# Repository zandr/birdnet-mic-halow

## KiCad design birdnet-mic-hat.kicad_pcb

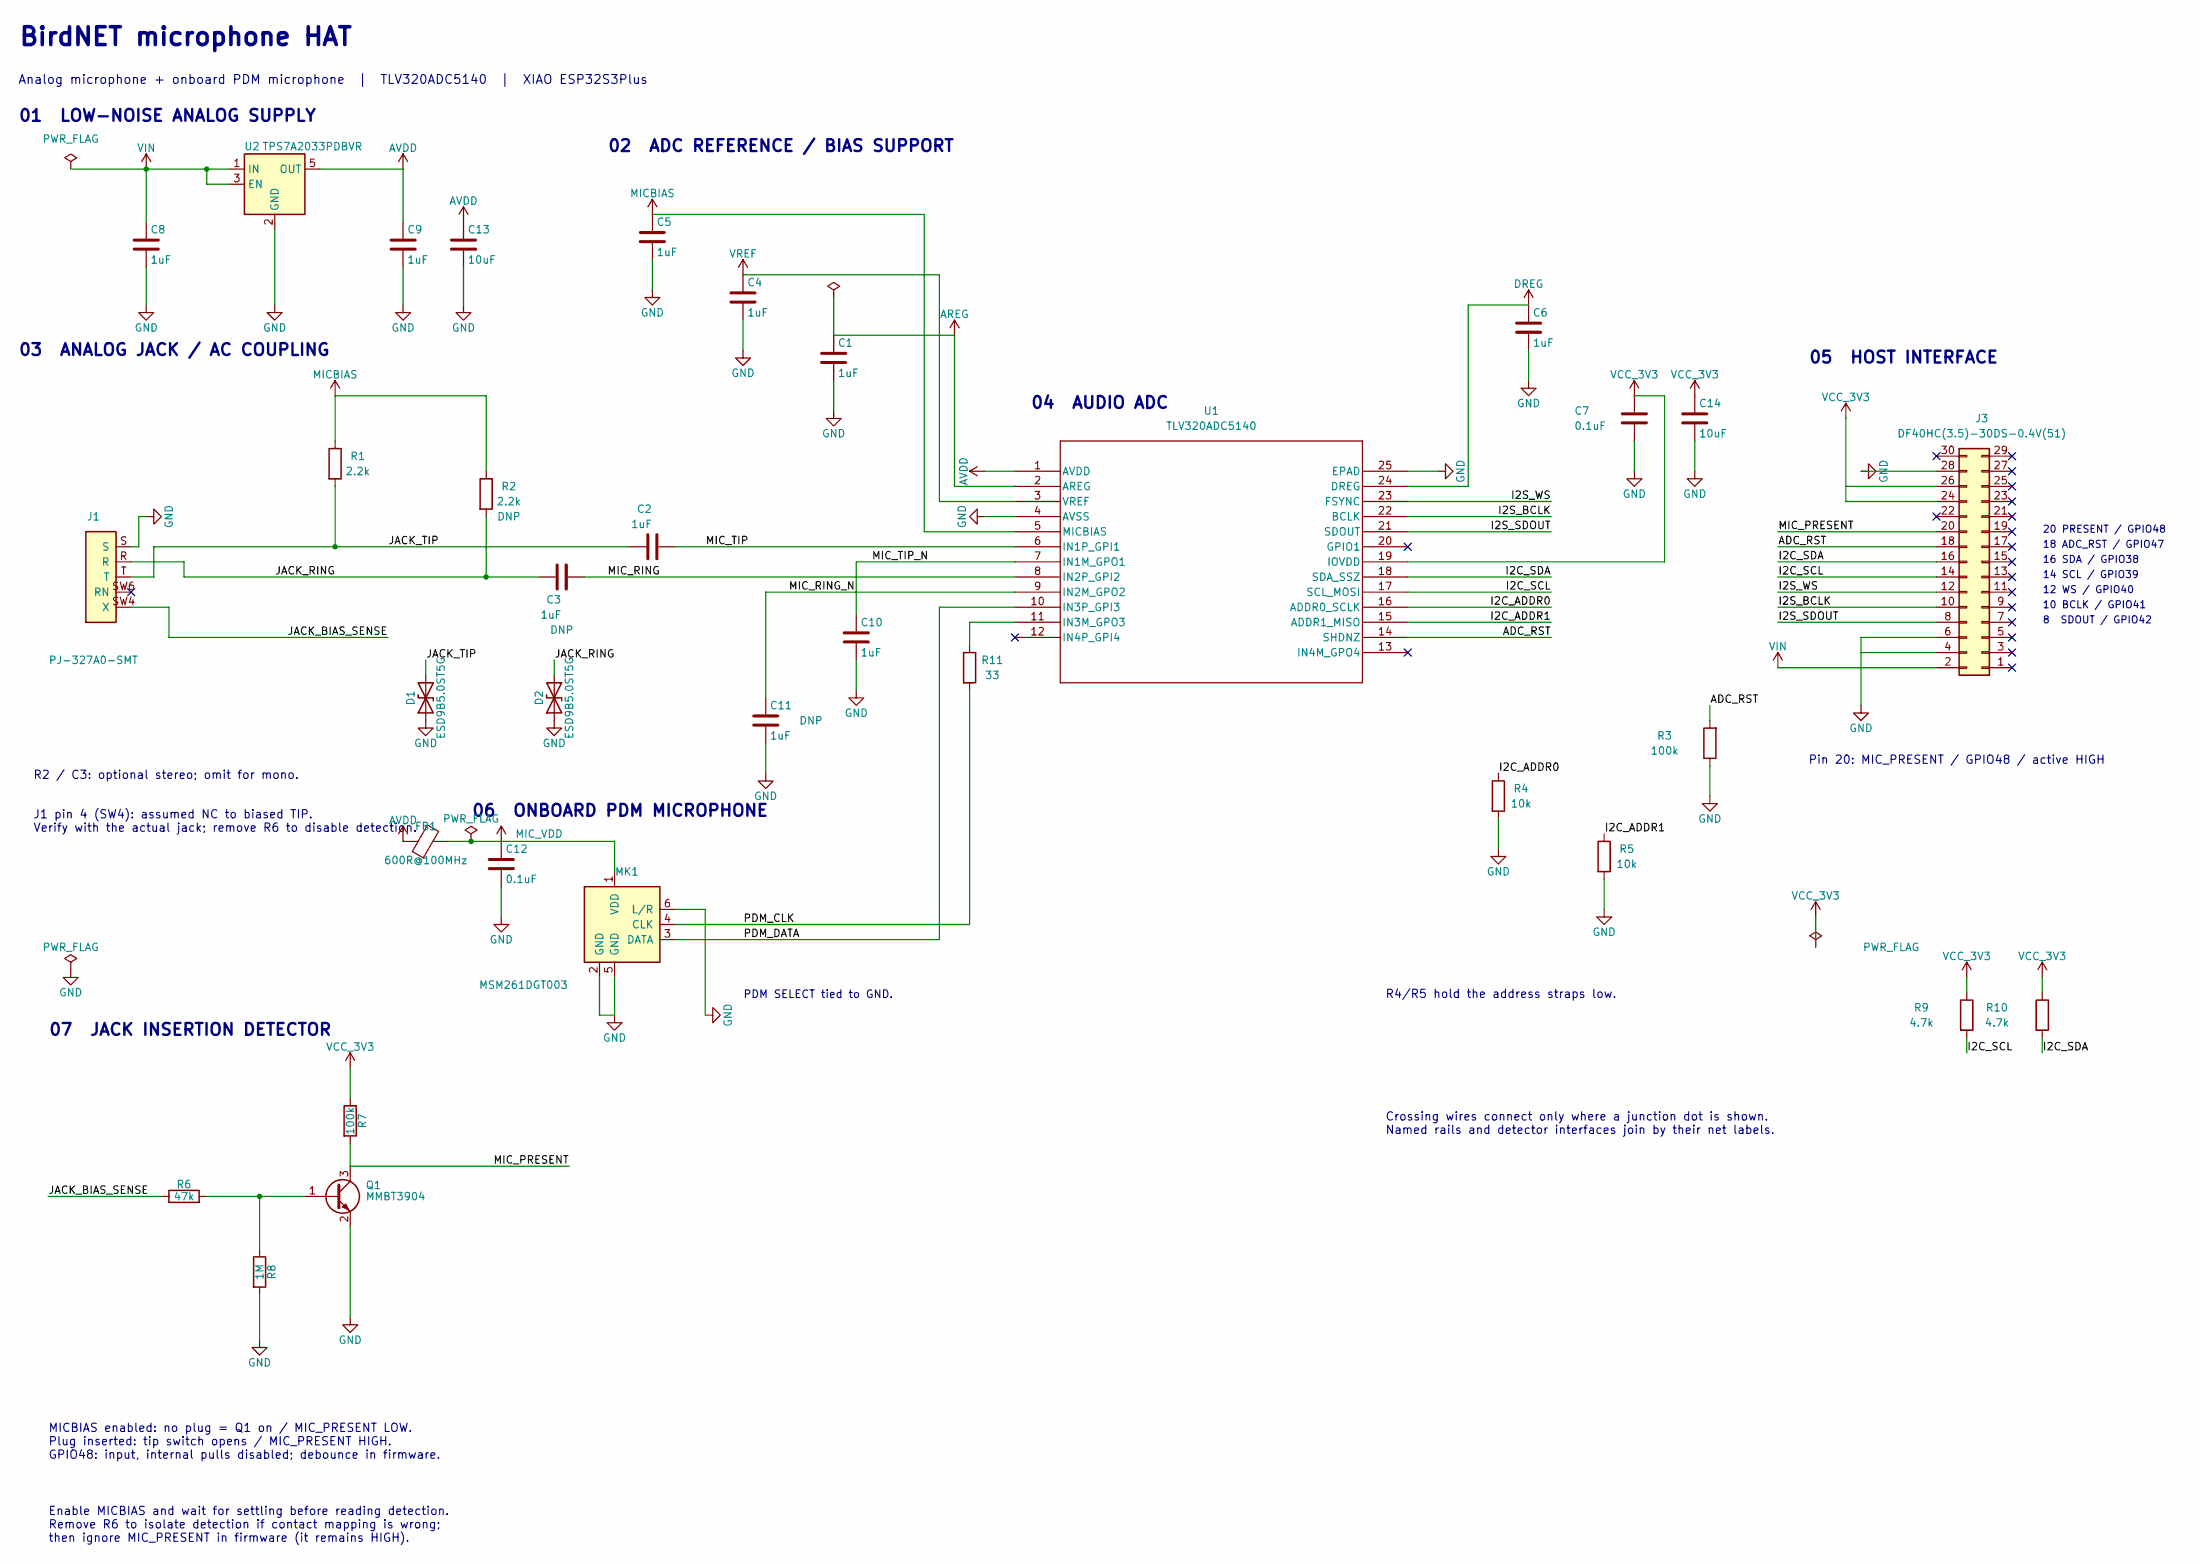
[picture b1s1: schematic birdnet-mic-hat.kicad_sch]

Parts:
C1, C4, C5, C6, C8, C9: 1uF; C_0402_1005Metric
C2, C3, C10, C11: 1uF; C_0603_1608Metric
C7, C12: 0.1uF; C_0402_1005Metric
C13, C14: 10uF; C_0603_1608Metric; MPN CL10A106KP8NNNC; LCSC C19702
D1, D2: ESD9B5.0ST5G; D_SOD-923; MPN ESD9B5.0ST5G; LCSC C111566
FB1: 600R@100MHz; L_0402_1005Metric; MPN BLM15PX601SN1D; LCSC C160977
J1: PJ-327A0-SMT; Jack_3.5mm_PJ-327A0-SMT; LCSC C381135
J3: DF40HC(3.5)-30DS-0.4V(51); DF40_30_LongWave_Hat
MK1: MSM261DGT003; MPN MSM261DGT003; LCSC C48227730
Q1: MMBT3904; SOT-23; MPN MMBT3904; LCSC C20526
R1, R2: 2.2k; R_0402_1005Metric
R3, R7: 100k; R_0402_1005Metric
R4, R5: 10k; R_0402_1005Metric
R6: 47k; R_0402_1005Metric
R8: 1M; R_0402_1005Metric
R9, R10: 4.7k; R_0402_1005Metric
R11: 33; R_0402_1005Metric
U1: TLV320ADC5140; RTW24_4P15X4P15_TEX
U2: TPS7A2033PDBVR; SOT-23-5

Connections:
/ADC_RST: J3.18, R3.2, U1.14 (SHDNZ)
/I2C_ADDR0: R4.1, U1.16 (ADDR0_SCLK)
/I2C_ADDR1: R5.1, U1.15 (ADDR1_MISO)
/I2C_SCL: J3.14, R9.2, U1.17 (SCL_MOSI)
/I2C_SDA: J3.16, R10.2, U1.18 (SDA_SSZ)
/I2S_BCLK: J3.10, U1.22 (BCLK)
/I2S_SDOUT: J3.8, U1.21 (SDOUT)
/I2S_WS: J3.12, U1.23 (FSYNC)
/JACK_BIAS_SENSE: J1.SW4 (X), R6.1
/JACK_RING: C3.1, D2.2 (A2), J1.R, R2.2
/JACK_TIP: C2.1, D1.2 (A2), J1.T, R1.2
/MIC_PRESENT: J3.20, Q1.3 (C), R7.2
/MIC_RING: C3.2, U1.8 (IN2P_GPI2)
/MIC_RING_N: C11.1, U1.9 (IN2M_GPO2)
/MIC_TIP: C2.2, U1.6 (IN1P_GPI1)
/MIC_TIP_N: C10.1, U1.7 (IN1M_GPO1)
/PDM_CLK: MK1.4 (CLK), R11.2
/PDM_DATA: MK1.3 (DATA), U1.10 (IN3P_GPI3)
AREG: C1.1, U1.2 (AREG)
AVDD: C9.1, C13.1, FB1.1, U1.1 (AVDD), U2.5 (OUT)
DREG: C6.1, U1.24 (DREG)
GND: C1.2, C4.2, C5.2, C6.2, C7.2, C8.2, C9.2, C10.2, C11.2, C12.2, C13.2, C14.2, D1.1 (A1), D2.1 (A1), J1.S, J3.4, J3.6, J3.28, MK1.2 (GND), MK1.5 (GND), MK1.6 (L/R), Q1.2 (E), R3.1, R4.2, R5.2, R8.2, U1.4 (AVSS), U1.25 (EPAD), U2.2 (GND)
MICBIAS: C5.1, R1.1, R2.1, U1.5 (MICBIAS)
MIC_VDD: C12.1, FB1.2, MK1.1 (VDD)
unnamed: Q1.1 (B), R6.2, R8.1
unnamed: R11.1, U1.11 (IN3M_GPO3)
VCC_3V3: C7.1, C14.1, J3.24, J3.26, R7.1, R9.1, R10.1, U1.19 (IOVDD)
VIN: C8.1, J3.2, U2.1 (IN), U2.3 (EN)
VREF: C4.1, U1.3 (VREF)

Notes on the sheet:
R4/R5 hold the address straps low.
02 ADC REFERENCE / BIAS SUPPORT
16 SDA / GPIO38
12 WS / GPIO40
8 SDOUT / GPIO42
Pin 20: MIC_PRESENT / GPIO48 / active HIGH
14 SCL / GPIO39
01 LOW-NOISE ANALOG SUPPLY
06 ONBOARD PDM MICROPHONE
R2 / C3: optional stereo; omit for mono.
18 ADC_RST / GPIO47
MICBIAS enabled: no plug = Q1 on / MIC_PRESENT LOW. Plug inserted: tip switch opens / MIC_PRESENT HIGH. GPIO48: input, internal pulls disabled; debounce in firmware.
J1 pin 4 (SW4): assumed NC to biased TIP. Verify with the actual jack; remove R6 to disable detection.
20 PRESENT / GPIO48
10 BCLK / GPIO41
04 AUDIO ADC
PDM SELECT tied to GND.
BirdNET microphone HAT
Enable MICBIAS and wait for settling before reading detection. Remove R6 to isolate detection if contact mapping is wrong; then ignore MIC_PRESENT in firmware (it remains HIGH).
03 ANALOG JACK / AC COUPLING
Crossing wires connect only where a junction dot is shown. Named rails and detector interfaces join by their net labels.
Analog microphone + onboard PDM microphone | TLV320ADC5140 | XIAO ESP32S3Plus
07 JACK INSERTION DETECTOR
05 HOST INTERFACE

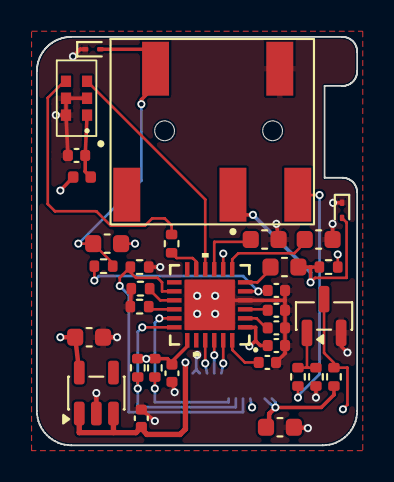
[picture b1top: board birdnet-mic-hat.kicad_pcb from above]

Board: 4 copper layers, 17.8 x 22.7 mm, 34 parts (1 on the bottom side), 29 nets.

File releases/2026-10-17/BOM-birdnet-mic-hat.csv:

Comment,Designator,Footprint,LCSC Part #,MPN,Manufacturer,Quantity
1uF,"C1,C4,C5,C6,C8,C9",Capacitor_SMD:C_0402_1005Metric,C167339,0402X105K160NT,FH,6
1uF,"C2,C10",Capacitor_SMD:C_0603_1608Metric,C106248,CC0603KRX7R7BB105,YAGEO,2
0.1uF,"C7,C12",Capacitor_SMD:C_0402_1005Metric,C60474,CC0402KRX7R7BB104,YAGEO,2
PJ-327A0-SMT,J1,BirdNetMicHat:Jack_3.5mm_PJ-327A0-SMT,C381135,PJ-327A0-SMT,XKB Connection,1
DF40HC(3.5)-30DS-0.4V(51),J3,BirdNetMicHat:DF40_30_LongWave_Hat,C597945,DF40HC(3.5)-30DS-0.4V(51),Hirose,1
MSM261DGT003,MK1,BirdNetMicHat:MSM261DGT003,C48227730,MSM261DGT003,MEMS,1
MMBT3904,Q1,Package_TO_SOT_SMD:SOT-23,C20526,MMBT3904,JSCJ,1
2.2k,R1,Resistor_SMD:R_0402_1005Metric,C25879,0402WGF2201TCE,UNI-ROYAL,1
10k,"R3,R4,R5",Resistor_SMD:R_0402_1005Metric,C25744,0402WGF1002TCE,UNI-ROYAL,3
47k,R6,Resistor_SMD:R_0402_1005Metric,C25792,0402WGF4702TCE,UNI-ROYAL,1
100k,R7,Resistor_SMD:R_0402_1005Metric,C25741,0402WGF1003TCE,UNI-ROYAL,1
1M,R8,Resistor_SMD:R_0402_1005Metric,C26083,0402WGF1004TCE,UNI-ROYAL,1
TLV320ADC5140,U1,ADC5140_FP:RTW24_4P15X4P15_TEX,,TLV320ADC5140IRTWR,Texas Instruments,1
TPS7A2033PDBVR,U2,Package_TO_SOT_SMD:SOT-23-5,C2862740,TPS7A2033PDBVR,Texas Instruments,1
